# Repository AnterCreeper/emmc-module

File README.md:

# eMMC Module

本项目为四层 eMMC 模块 PCB，采用 BGA-153 eMMC 和 GB042-34S 连接器。适配 Radxa ROCK 3/4/5 系列、ODROID N2/C4/XU4 系列、Orange Pi 5 Plus/5 Pro/3B/4 Pro、Pine64 RockPro64 等使用 GB042 34-pin eMMC 接口的板卡。

## 文件

| 文件 | 内容 |
| --- | --- |
| `emmc-module.kicad_pro` | 工程入口，KiCad 9 |
| `emmc-module.kicad_sch` | 原理图 |
| `emmc-module.kicad_pcb` | 四层 PCB |
| `emmc-module.kicad_sym` | 项目符号库 |
| `emmc-module.pretty/` | GB042 连接器封装 |
| `emmc-module-schematic.pdf` | 原理图导出 |
| `docs/GB040.pdf` | GB040 系列 0.4 mm BTB 连接器规格书（aitendo） |

## 设计说明

### NC 球位复用

本设计利用 BGA-153 的 NC 球位增加扇出：

| U1 球位 | 网络 |
| --- | --- |
| B1 | DAT3 |
| B7 | DAT7 |
| C1 | VDDI |
| C3 | DAT4 |
| C5 | DAT6 |
| C8 | DAT7 |
| D2 | DAT4 |
| D4 | GND |
| N1 | GND |
| N3 | VCCQ |
| P1 | GND |
| P2 | GND |

U1 的 C5 指 BGA 球位；原理图中另有一个去耦电容 C5 接 VCCQ，两者不是同一个器件。

这些球位在不同 eMMC 料号上可能是 NC、RFU 或厂商自定义功能。更换料号前按 datasheet 核对，不能只凭 BGA-153 封装相同就判断兼容。

### 连接器

J1 为 GB042-34S-H10-E3000，属于 GB040 系列，规格书见 `docs/GB040.pdf`：

- VCCQ：20、21
- VCC：22、23
- RST_N：12，板上没有上拉电阻
- DS：15
- DAT0/1/2/3/4/5/6/7：6、29、27、10、4、2、33、31
- CLK：8；CMD：25
- 其余引脚为 GND

### 去耦

- C1：0.1 uF，VDDI
- C2、C4、C5：0.1 uF，VCCQ
- C3、C6：0.1 uF，VCC

### 投板叠层

投板使用 JLC04081H-3313 叠层：四层、0.8 mm。信号线宽 0.1524 mm，按 50 Ω 单端阻抗设计。

## 验证

已完成打板，成品通过 Radxa eMMC Reader 的实机读写测试。

在 KiCad 9.0.2 下执行：

```bash
kicad-cli pcb drc --format json --severity-all -o /tmp/emmc-module-drc.json emmc-module.kicad_pcb
```

结果为 0 条违规、0 个未连接项。工程中 `starved_thermal` 和 `silk_edge_clearance` 设为 ignore。

加 `--schematic-parity` 会报告 12 条 `net_conflict`，对应上表 12 个球位。这是原理图符号与 PCB 网络的有意差异，不是连接错误；不要把这些焊盘改回 unconnected 来消除告警。

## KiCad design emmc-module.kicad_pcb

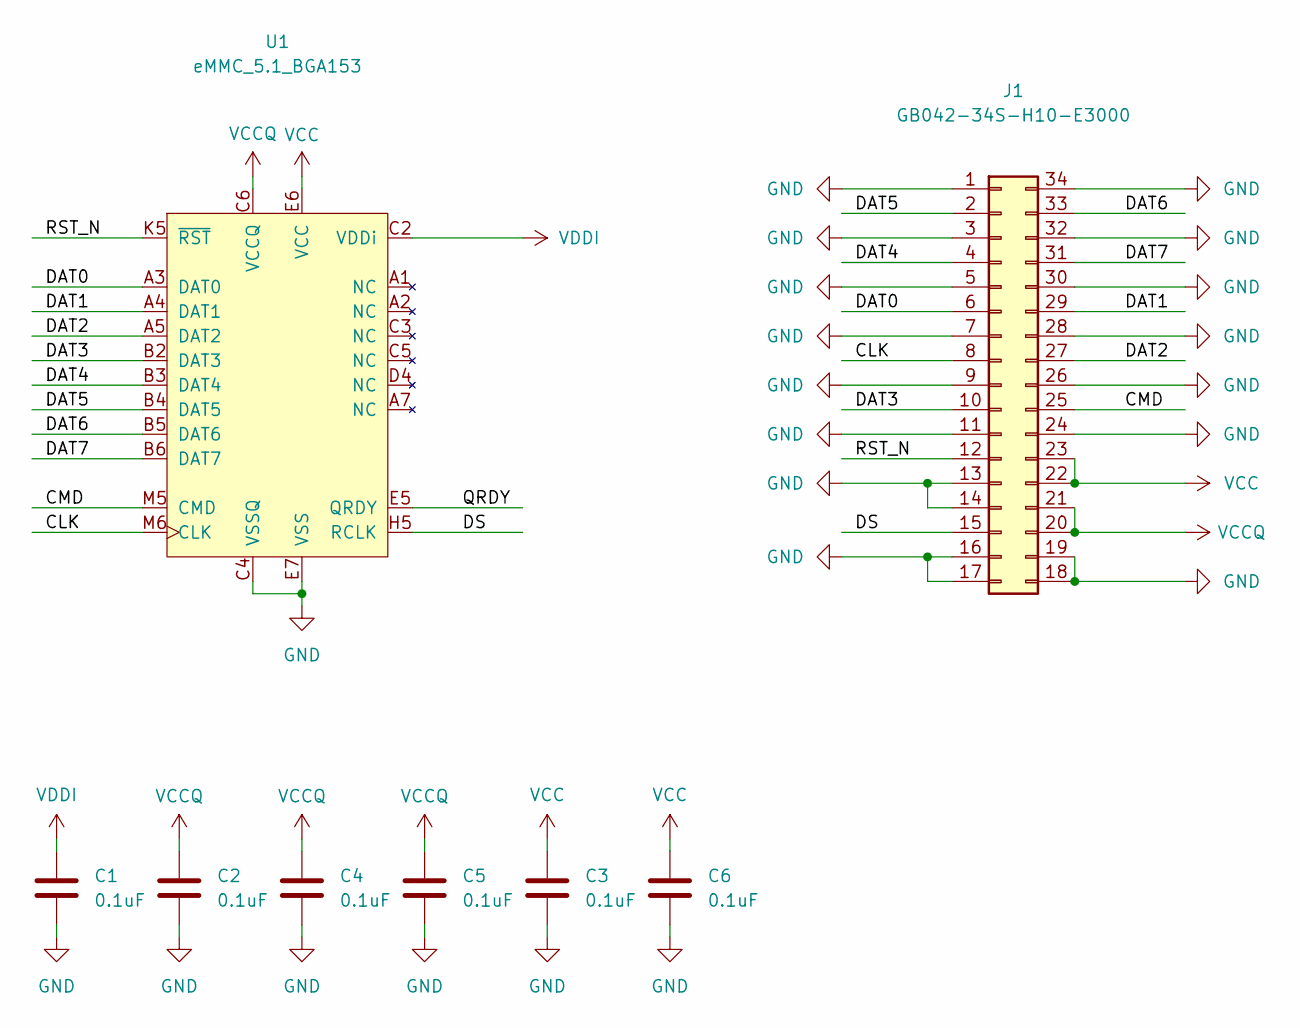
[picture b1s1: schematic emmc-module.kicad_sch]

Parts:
C1, C2, C3, C4, C5, C6: 0.1uF; C_0402_1005Metric
J1: GB042-34S-H10-E3000
U1: eMMC_5.1_BGA153; LFBGA-153_11.5x13mm_Layout14x14_P0.5mm

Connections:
/CLK: J1.8, U1.M6 (CLK)
/CMD: J1.25, U1.M5 (CMD)
/DAT0: J1.6, U1.A3 (DAT0)
/DAT1: J1.29, U1.A4 (DAT1)
/DAT2: J1.27, U1.A5 (DAT2)
/DAT3: J1.10, U1.B1, U1.B2 (DAT3)
/DAT4: J1.4, U1.B3 (DAT4), U1.C3 (NC), U1.D2
/DAT5: J1.2, U1.B4 (DAT5)
/DAT6: J1.33, U1.B5 (DAT6), U1.C5 (NC)
/DAT7: J1.31, U1.B6 (DAT7), U1.B7, U1.C8
/DS: J1.15, U1.H5 (RCLK)
/QRDY: U1.E5 (QRDY)
/RST_N: J1.12, U1.K5 (~RST)
GND: C1.1, C2.1, C3.1, C4.1, C5.1, C6.1, J1.1, J1.3, J1.5, J1.7, J1.9, J1.11, J1.13, J1.14, J1.16, J1.17, J1.18, J1.19, J1.24, J1.26, J1.28, J1.30, J1.32, J1.34, U1.A6 (VSS), U1.C4 (VSSQ), U1.D4 (NC), U1.E7 (VSS), U1.G5 (VSS), U1.H10 (VSS), U1.J5 (VSS), U1.K8 (VSS), U1.N1, U1.N2 (VSSQ), U1.N5 (VSSQ), U1.P1, U1.P2, U1.P4 (VSSQ), U1.P6 (VSSQ)
VCC: C3.2, C6.2, J1.22, J1.23, U1.E6 (VCC), U1.F5 (VCC), U1.J10 (VCC), U1.K9 (VCC)
VCCQ: C2.2, C4.2, C5.2, J1.20, J1.21, U1.C6 (VCCQ), U1.M4 (VCCQ), U1.N3, U1.N4 (VCCQ), U1.P3 (VCCQ), U1.P5 (VCCQ)
VDDI: C1.2, U1.C1, U1.C2 (VDDi)

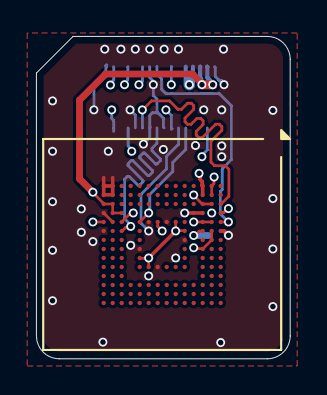
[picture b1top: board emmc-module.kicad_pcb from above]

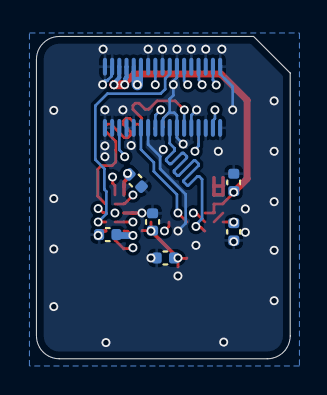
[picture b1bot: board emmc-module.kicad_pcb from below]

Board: 4 copper layers, 14.1 x 17.9 mm, 8 parts (7 on the bottom side), 16 nets.
